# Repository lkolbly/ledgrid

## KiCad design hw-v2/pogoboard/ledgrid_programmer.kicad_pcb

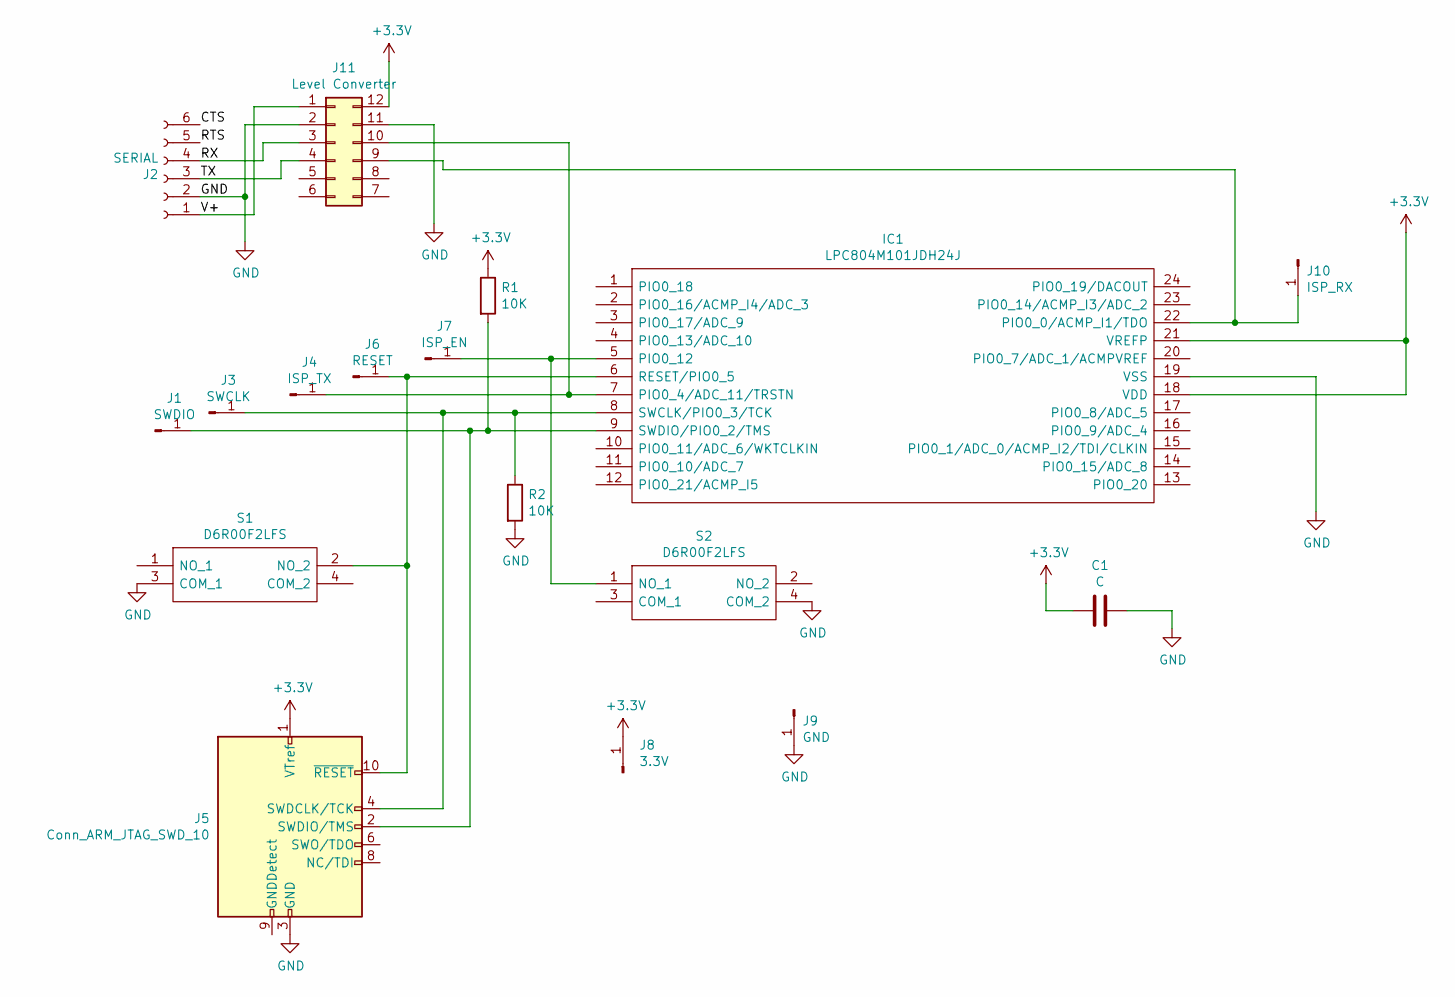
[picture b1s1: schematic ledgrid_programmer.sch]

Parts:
C1: C; C_0805_2012Metric_Pad1.15x1.40mm_HandSolder
IC1: LPC804M101JDH24J; SOP65P640X110-24N; Manufacturer_Part_Number LPC804M101JDH24J
J1: SWDIO; PinHeader_1x01_P2.54mm_Vertical
J2: SERIAL; PinHeader_1x06_P2.54mm_Vertical
J3: SWCLK; PinHeader_1x01_P2.54mm_Vertical
J4: ISP_TX; PinHeader_1x01_P2.54mm_Vertical
J5: Conn_ARM_JTAG_SWD_10; PinHeader_2x05_P2.54mm_Vertical
J6: RESET; PinHeader_1x01_P2.54mm_Vertical
J7: ISP_EN; PinHeader_1x01_P2.54mm_Vertical
J8: 3.3V; PinHeader_1x01_P2.54mm_Vertical
J9: GND; PinHeader_1x01_P2.54mm_Vertical
J10: ISP_RX; PinHeader_1x01_P2.54mm_Vertical
J11: Level Converter; DIP-12_W10.16mm
R1, R2: 10K; R_Axial_DIN0207_L6.3mm_D2.5mm_P7.62mm_Horizontal
S1, S2: D6R00F2LFS; Mouser Part Number 611-D6R00F2LFS

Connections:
+3V3: C1.2, IC1.18 (VDD), IC1.21 (VREFP), J5.1 (VTref), J8.1, J11.12, R1.1
/CTS: J2.6
/RTS: J2.5
/RX: J2.4, J11.3
/TX: J2.3, J11.4
/V+: J2.1, J11.1
GND: C1.1, IC1.19 (VSS), J2.2, J5.3 (GND), J5.5 (GND), J9.1, J11.2, J11.11, R2.2, S1.3 (COM_1), S2.4 (COM_2)
unnamed: IC1.5 (PIO0_12), J7.1, S2.1 (NO_1)
unnamed: IC1.6 (RESET/PIO0_5), J5.10 (~RESET~), J6.1, S1.2 (NO_2)
unnamed: IC1.7 (PIO0_4/ADC_11/TRSTN), J4.1, J11.10
unnamed: IC1.8 (SWCLK/PIO0_3/TCK), J3.1, J5.4 (SWDCLK/TCK), R2.1
unnamed: IC1.9 (SWDIO/PIO0_2/TMS), J1.1, J5.2 (SWDIO/TMS), R1.2
unnamed: IC1.22 (PIO0_0/ACMP_I1/TDO), J10.1, J11.9

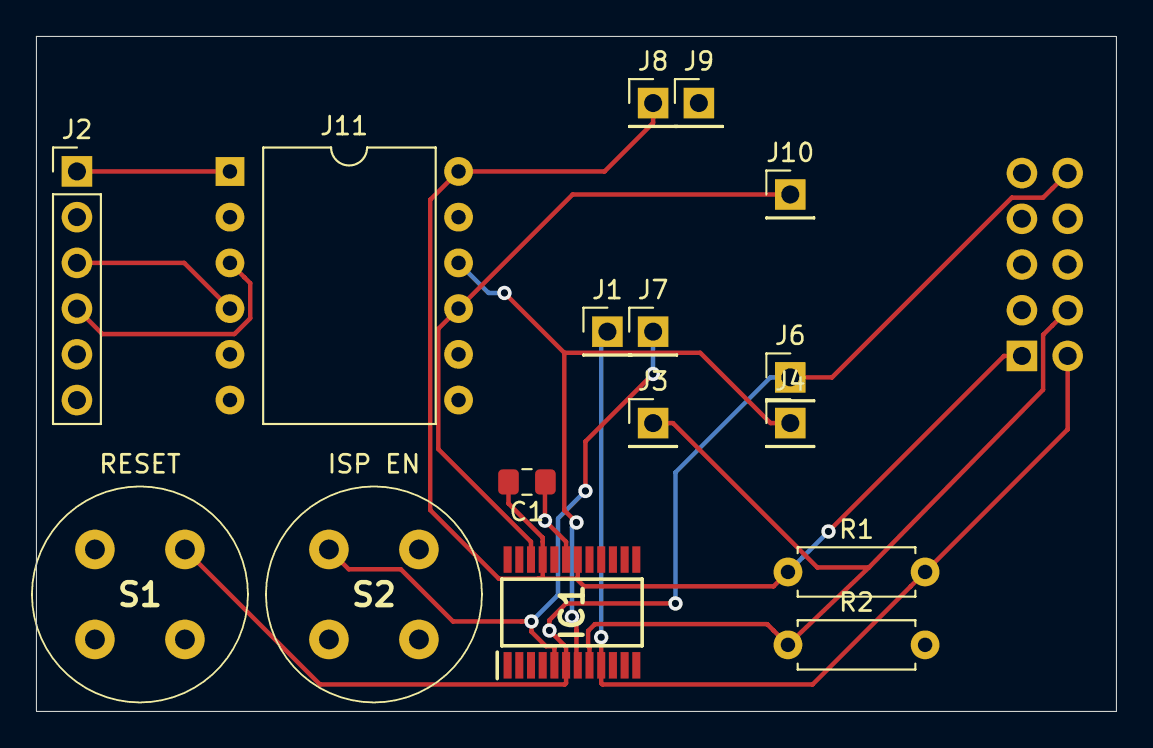
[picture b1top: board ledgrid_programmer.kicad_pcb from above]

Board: 2 copper layers, 60.0 x 37.5 mm, 17 parts (1 on the bottom side), 11 nets.

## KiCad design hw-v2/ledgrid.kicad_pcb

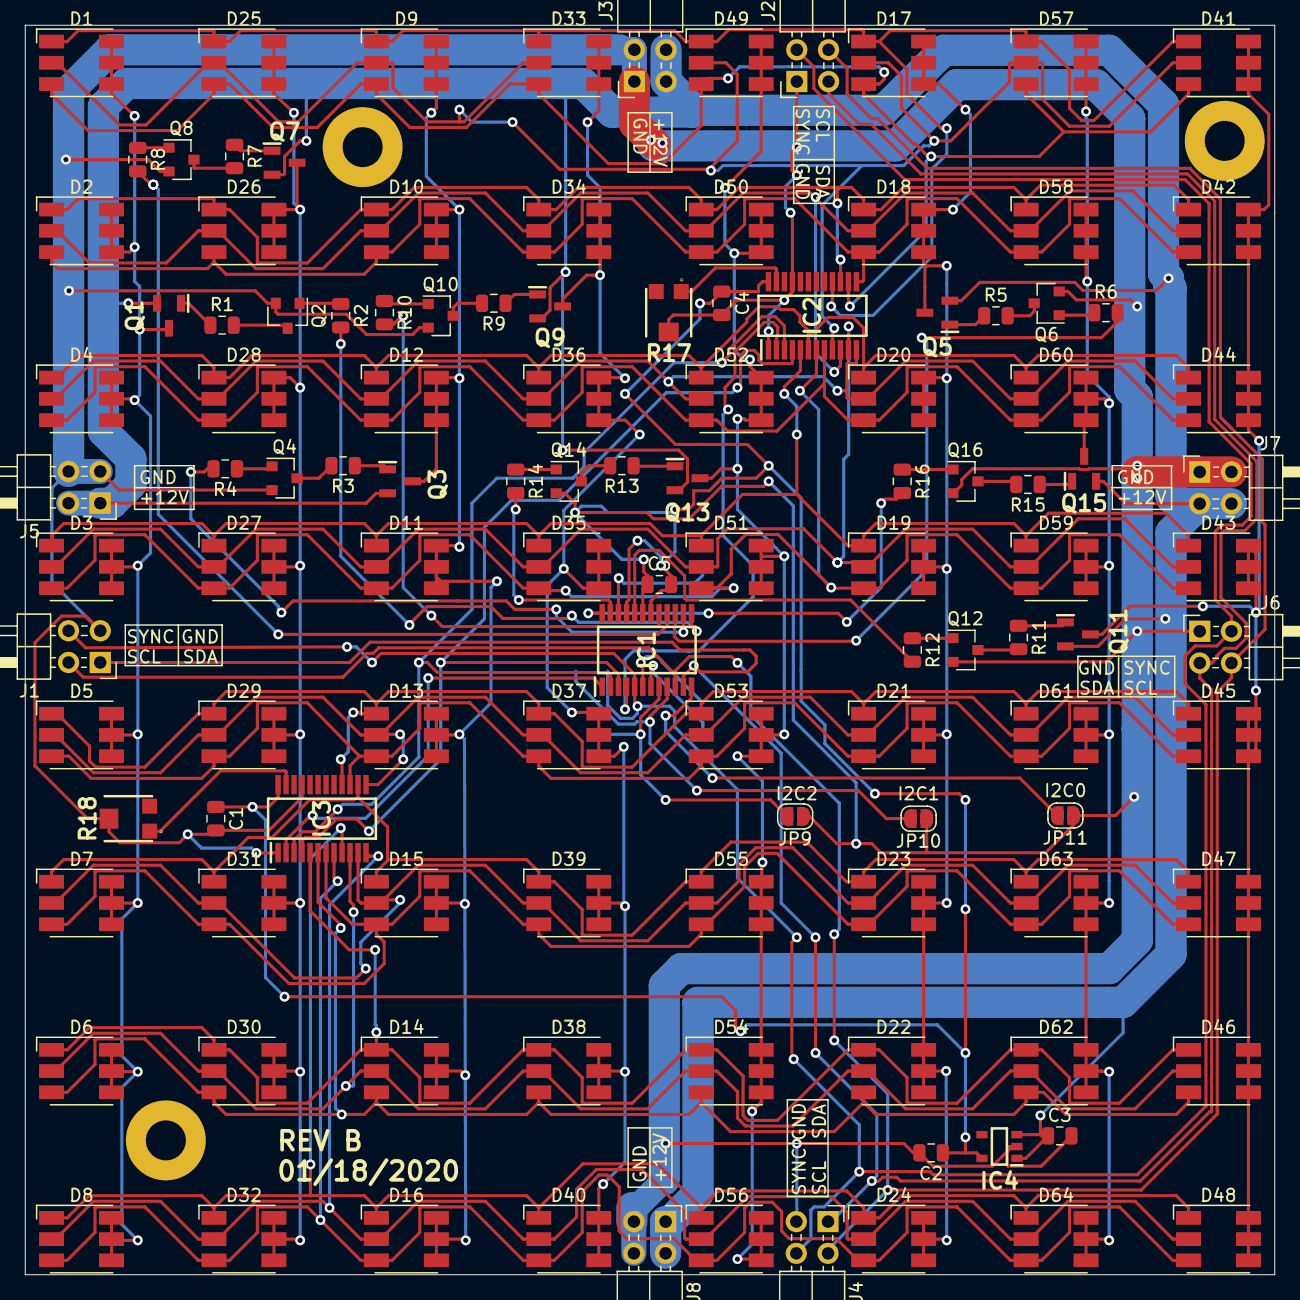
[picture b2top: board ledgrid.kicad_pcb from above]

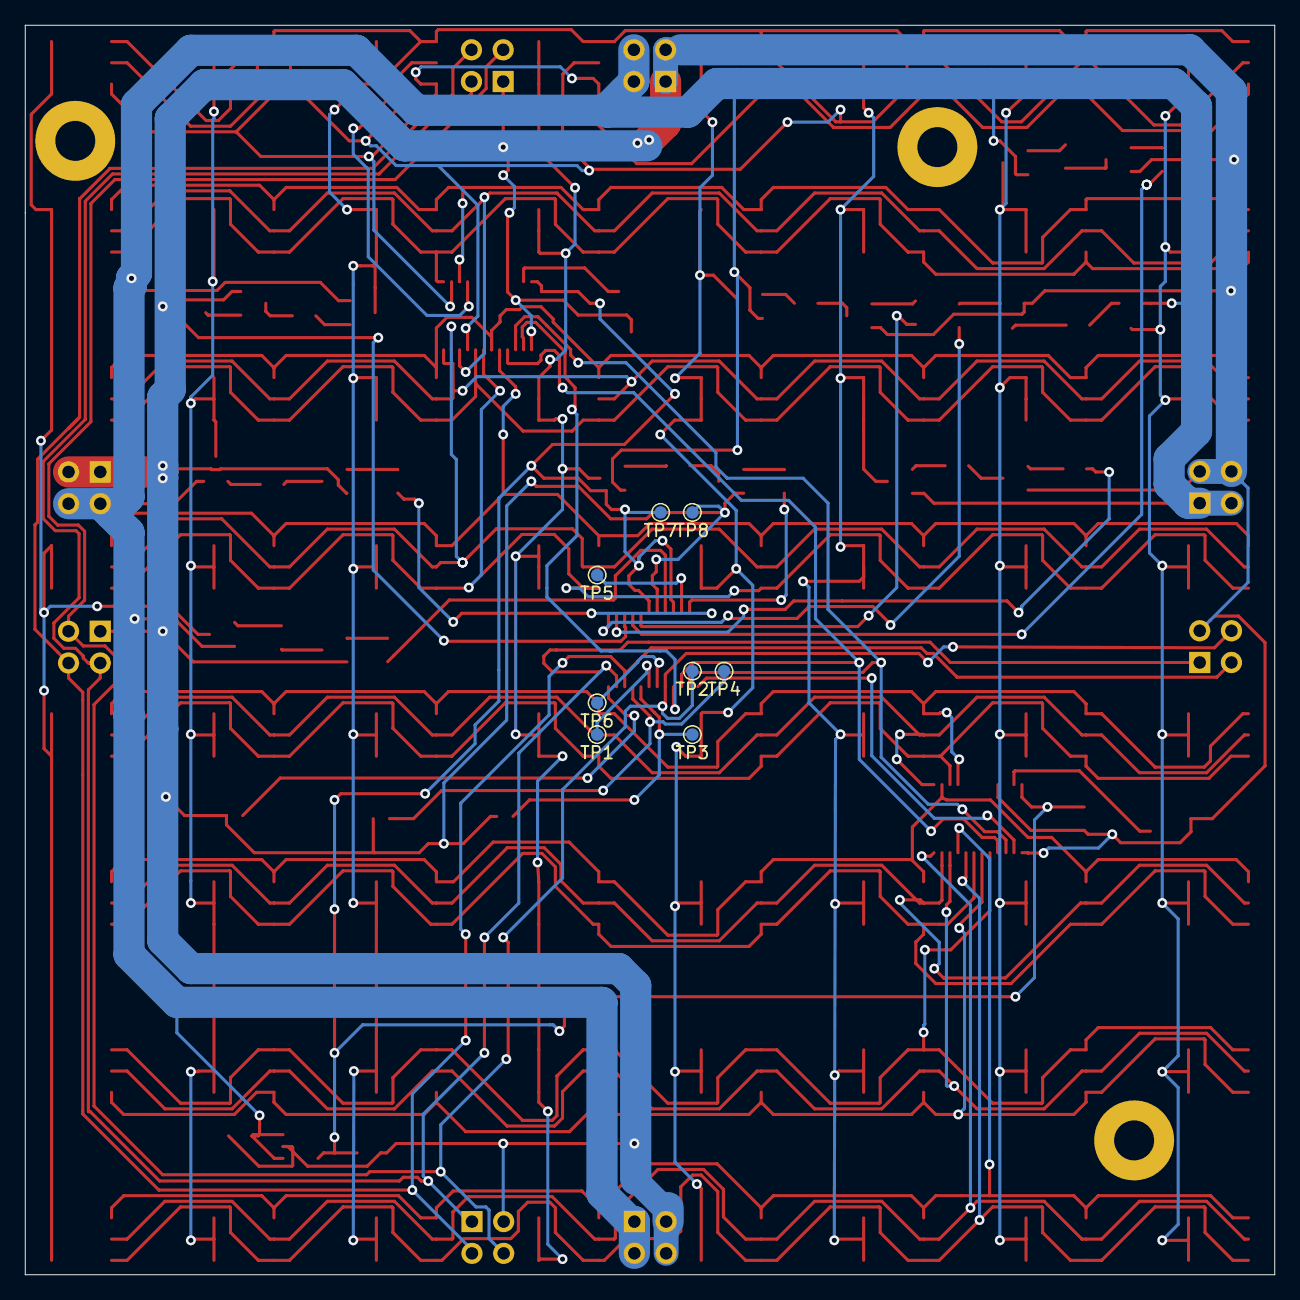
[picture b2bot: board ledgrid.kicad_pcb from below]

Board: 2 copper layers, 100.0 x 100.0 mm, 126 parts (8 on the bottom side), 82 nets.

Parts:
C1, C2: 4.7u; C_0805_2012Metric
C3, C4, C5: 4.7uF; C_0805_2012Metric
D1, D2, D3, D4, D5, D6, D7, D8, D9, D10, D11, D12, D13, D14, D15, D16, D17, D18, D19, D20, D21, D22, D23, D24, D25, D26, D27, D28, D29, D30, D31, D32, D33, D34, D35, D36, D37, D38, D39, D40, D41, D42, D43, D44, D45, D46, D47, D48, D49, D50, D51, D52, D53, D54, D55, D56, D57, D58, D59, D60, D61, D62, D63, D64: LED_RGB; LED_RGB_5050-6
IC1: LPC804M101JDH24J; SOP65P640X110-24N
IC2, IC3: TC62D748CFNAG(CEBH; SOP64P600X175-24N
IC4: NJM2866F33-TE1; SOT95P280X130-5N
J1, J2, J4, J6: PWR_I2C; PinHeader_2x02_P2.54mm_Horizontal
J3, J5, J7, J8: PWR_BULK; PinHeader_2x02_P2.54mm_Horizontal
JP9: I2C2; SolderJumper-2_P1.3mm_Open_RoundedPad1.0x1.5mm
JP10: I2C1; SolderJumper-2_P1.3mm_Open_RoundedPad1.0x1.5mm
JP11: I2C0; SolderJumper-2_P1.3mm_Open_RoundedPad1.0x1.5mm
Q1, Q3, Q5, Q7, Q9, Q11, Q13, Q15: MMSS8550-L-TP; SOT96P237X122-3N
Q2, Q4, Q6, Q8, Q10, Q12, Q14, Q16: BC850; SOT-23
R1, R2, R3, R4, R5, R6, R7, R8, R9, R10, R11, R12, R13, R14, R15, R16: 1K; R_0805_2012Metric
R17, R18: TC33X-2-103E; TC33X-2_1
TP1: ISP TX; TestPoint_Pad_D1.0mm
TP2: ISP_EN; TestPoint_Pad_D1.0mm
TP3: SWCLK; TestPoint_Pad_D1.0mm
TP4: SWDIO; TestPoint_Pad_D1.0mm
TP5: ISP RX; TestPoint_Pad_D1.0mm
TP6: RESET; TestPoint_Pad_D1.0mm
TP7: 3.3V; TestPoint_Pad_D1.0mm
TP8: GND; TestPoint_Pad_D1.0mm

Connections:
+3V3: C1.1, C2.1, C4.1, C5.2, IC1.18, IC1.21, IC2.24, IC3.24, IC4.5, TP7.1
+12V: C3.1, IC4.1, IC4.3, J3.3, J3.4, J5.1, J5.2, J7.3, J7.4, J8.1, J8.2, Q1.2, Q3.2, Q5.2, Q7.2, Q9.2, Q11.2, Q13.2, Q15.2
/COL0: IC1.13, R2.2
/COL1: IC1.14, R4.2
/COL2: IC1.15, R6.2
/COL3: IC1.16, R8.2
/COL4: IC1.17, R10.2
/COL5: IC1.20, R12.2
/COL6: IC1.23, R14.2
/COL7: IC1.24, R16.2
/Shift Registers/a0: D1.1, D9.1, D17.1, D25.1, D33.1, D41.1, D49.1, D57.1, IC2.16
/Shift Registers/a1: D2.1, D10.1, D18.1, D26.1, D34.1, D42.1, D50.1, D58.1, IC2.15
/Shift Registers/a2: D3.1, D11.1, D19.1, D27.1, D35.1, D43.1, D51.1, D59.1, IC2.5
/Shift Registers/a3: D4.1, D12.1, D20.1, D28.1, D36.1, D44.1, D52.1, D60.1, IC2.6
/Shift Registers/a4: D5.1, D13.1, D21.1, D29.1, D37.1, D45.1, D53.1, D61.1, IC3.16
/Shift Registers/a5: D6.1, D14.1, D22.1, D30.1, D38.1, D46.1, D54.1, D62.1, IC3.5
/Shift Registers/a6: D7.1, D15.1, D23.1, D31.1, D39.1, D47.1, D55.1, D63.1, IC3.14
/Shift Registers/a7: D8.1, D16.1, D24.1, D32.1, D40.1, D48.1, D56.1, D64.1, IC3.9
/Shift Registers/b0: D1.2, D9.2, D17.2, D25.2, D33.2, D41.2, D49.2, D57.2, IC2.9
/Shift Registers/b1: D2.2, D10.2, D18.2, D26.2, D34.2, D42.2, D50.2, D58.2, IC2.10
/Shift Registers/b2: D3.2, D11.2, D19.2, D27.2, D35.2, D43.2, D51.2, D59.2, IC2.11
/Shift Registers/b3: D4.2, D12.2, D20.2, D28.2, D36.2, D44.2, D52.2, D60.2, IC2.12
/Shift Registers/b4: D5.2, D13.2, D21.2, D29.2, D37.2, D45.2, D53.2, D61.2, IC3.13
/Shift Registers/b5: D6.2, D14.2, D22.2, D30.2, D38.2, D46.2, D54.2, D62.2, IC3.10
/Shift Registers/b6: D7.2, D15.2, D23.2, D31.2, D39.2, D47.2, D55.2, D63.2, IC3.11
/Shift Registers/b7: D8.2, D16.2, D24.2, D32.2, D40.2, D48.2, D56.2, D64.2, IC3.12
/Shift Registers/c0: D1.3, D9.3, D17.3, D25.3, D33.3, D41.3, D49.3, D57.3, IC2.14
/Shift Registers/c1: D2.3, D10.3, D18.3, D26.3, D34.3, D42.3, D50.3, D58.3, IC2.13
/Shift Registers/c2: D3.3, D11.3, D19.3, D27.3, D35.3, D43.3, D51.3, D59.3, IC2.7
/Shift Registers/c3: D4.3, D12.3, D20.3, D28.3, D36.3, D44.3, D52.3, D60.3, IC2.8
/Shift Registers/c4: D5.3, D13.3, D21.3, D29.3, D37.3, D45.3, D53.3, D61.3, IC3.15
/Shift Registers/c5: D6.3, D14.3, D22.3, D30.3, D38.3, D46.3, D54.3, D62.3, IC3.6
/Shift Registers/c6: D7.3, D15.3, D23.3, D31.3, D39.3, D47.3, D55.3, D63.3, IC3.7
/Shift Registers/c7: D8.3, D16.3, D24.3, D32.3, D40.3, D48.3, D56.3, D64.3, IC3.8
GND: C1.2, C2.2, C3.2, C4.2, C5.1, IC1.19, IC2.1, IC2.21, IC3.1, IC3.21, IC4.2, J1.3, J2.1, J3.1, J3.2, J4.3, J5.3, J5.4, J6.1, J7.1, J7.2, J8.3, J8.4, JP9.1, JP10.1, JP11.1, Q2.2, Q4.2, Q6.2, Q8.2, Q10.2, Q12.2, Q14.2, Q16.2, R17.2, R18.2, TP8.1
unnamed: D1.4, D1.5, D1.6, D2.4, D2.5, D2.6, D3.4, D3.5, D3.6, D4.4, D4.5, D4.6, D5.4, D5.5, D5.6, D6.4, D6.5, D6.6, D7.4, D7.5, D7.6, D8.4, D8.5, D8.6, Q1.3
unnamed: D9.4, D9.5, D9.6, D10.4, D10.5, D10.6, D11.4, D11.5, D11.6, D12.4, D12.5, D12.6, D13.4, D13.5, D13.6, D14.4, D14.5, D14.6, D15.4, D15.5, D15.6, D16.4, D16.5, D16.6, Q3.3
unnamed: D17.4, D17.5, D17.6, D18.4, D18.5, D18.6, D19.4, D19.5, D19.6, D20.4, D20.5, D20.6, D21.4, D21.5, D21.6, D22.4, D22.5, D22.6, D23.4, D23.5, D23.6, D24.4, D24.5, D24.6, Q5.3
unnamed: D25.4, D25.5, D25.6, D26.4, D26.5, D26.6, D27.4, D27.5, D27.6, D28.4, D28.5, D28.6, D29.4, D29.5, D29.6, D30.4, D30.5, D30.6, D31.4, D31.5, D31.6, D32.4, D32.5, D32.6, Q7.3
unnamed: D33.4, D33.5, D33.6, D34.4, D34.5, D34.6, D35.4, D35.5, D35.6, D36.4, D36.5, D36.6, D37.4, D37.5, D37.6, D38.4, D38.5, D38.6, D39.4, D39.5, D39.6, D40.4, D40.5, D40.6, Q9.3
unnamed: D41.4, D41.5, D41.6, D42.4, D42.5, D42.6, D43.4, D43.5, D43.6, D44.4, D44.5, D44.6, D45.4, D45.5, D45.6, D46.4, D46.5, D46.6, D47.4, D47.5, D47.6, D48.4, D48.5, D48.6, Q11.3
unnamed: D49.4, D49.5, D49.6, D50.4, D50.5, D50.6, D51.4, D51.5, D51.6, D52.4, D52.5, D52.6, D53.4, D53.5, D53.6, D54.4, D54.5, D54.6, D55.4, D55.5, D55.6, D56.4, D56.5, D56.6, Q13.3
unnamed: D57.4, D57.5, D57.6, D58.4, D58.5, D58.6, D59.4, D59.5, D59.6, D60.4, D60.5, D60.6, D61.4, D61.5, D61.6, D62.4, D62.5, D62.6, D63.4, D63.5, D63.6, D64.4, D64.5, D64.6, Q15.3
unnamed: IC1.6, TP6.1
unnamed: IC1.7, TP1.1
unnamed: IC1.8, JP9.2, TP3.1
unnamed: IC1.9, JP10.2, TP4.1
unnamed: IC1.12, JP11.2
unnamed: IC1.22, TP5.1
unnamed: IC2.23, R17.1
unnamed: IC3.23, R18.1
unnamed: Q1.1, R1.1
unnamed: Q2.1, R2.1
unnamed: Q2.3, R1.2
unnamed: Q3.1, R3.1
unnamed: Q4.1, R4.1
unnamed: Q4.3, R3.2
unnamed: Q5.1, R5.1
unnamed: Q6.1, R6.1
unnamed: Q6.3, R5.2
unnamed: Q7.1, R7.1
unnamed: Q8.1, R8.1
unnamed: Q8.3, R7.2
unnamed: Q9.1, R9.1
unnamed: Q10.1, R10.1
unnamed: Q10.3, R9.2
unnamed: Q11.1, R11.1
unnamed: Q12.1, R12.1
unnamed: Q12.3, R11.2
unnamed: Q13.1, R13.1
unnamed: Q14.1, R14.1
unnamed: Q14.3, R13.2
unnamed: Q15.1, R15.1
unnamed: Q16.1, R16.1
unnamed: Q16.3, R15.2
SCK: IC1.2, IC2.3, IC3.3
SCL: IC1.10, J1.2, J2.4, J4.2, J6.4
SDA: IC1.11, J1.1, J2.3, J4.1, J6.3
SINA: IC1.1, IC3.2
SINB: IC1.4, IC2.2
SLAT: IC1.3, IC2.4, IC3.4
SYNC: IC1.5, J1.4, J2.2, J4.4, J6.2, TP2.1

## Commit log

2020-03-08 Add rev B ledgrid
    This is the surface mount refresh of the led grid project.
2020-03-08 Add pogoboard for rev B ledgrid
2020-03-22 Create pogoboard bracket
